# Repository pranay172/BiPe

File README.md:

# BiPe

BiPe is a small wheeled biped: two legs, a wheel at the end of each, and a
binocular head pod. It balances on its wheels, drives, turns, crouches and
stands, gets back up after a fall, and can follow a person wearing an
AprilTag. It is about 1.8 kg.

The robot was designed in full before anything is built: CAD with real parts,
circuit boards, firmware, a physics model and two controllers (a classical
one and a learned policy). **Everything here is simulation and design.
Nothing has been built or powered yet.** Results are labelled by what they
are: a layout study, a validated simulation under stated assumptions, or
(later) a hardware result.

The project takes its direction from open, sim-first robots such as Pollen
Robotics' [Microduck](https://github.com/pollen-robotics/microduck): train in
simulation, export a small policy, and publish the recipe so anyone can rerun
it.

## What it can do in simulation

All results are on the full MuJoCo plant: free base, finite motor limits,
physical contact, belt and gear lash, sensor delays and noise, and the same C
firmware the robot runs.

| Area | Result |
|---|---|
| Balance, drive, turn, crouch | A 107-case acceptance suite: pushes, belt and gear lash, mass and friction changes, motor lag, sensor delay and noise, slopes. Classical controller: all 70 robustness-matrix cases and 25 of 27 scenario cases. |
| Speed | 1.2 m/s, 1.25 m/s², 1.0 rad/s turns, 0.3 m/s reverse, on a 44-case speed suite. |
| Falls | Forward and backward tips keep a structural factor of at least 2.06 on every load path. |
| Electronics | Six moteus-c1 drivers on CAN-FD, a Teensy 4.0 carrier, power board; 3.44 ms of the 5 ms control budget; 28–39 min runtime. |
| Person following | Rendered camera frames in the loop with AprilTag detection: 60/60 nominal runs and 101/112 overall, no falls on the nominal plant. |
| Learned policy | Trained with mjlab on MuJoCo Warp. Recovers 89/98 acceptance cases (classical 83/98), all 30 pushes, all 8 belt-range cases, no physical failures, and survives all 92 cases of the M18 fidelity suite (motor, sensor, timing and floor imperfections; classical 88/92). Exported to ONNX and a 48k-parameter C forward pass that matches within 6.3e-7. |
| Get-up | A second policy gets the robot up from a sit or a front or back lean and hands over to the locomotion policy, including from flat on the face or back (M17: legs to their stops for 0.5 s first). M18's version, trained with motor, sensor, timing and floor imperfections: 60/60 held-out randomised falls, 40/40 on a fresh set, and 39/40 and 38/40 on two sets of robots drawn from those imperfections. |
| Sit and stand | A third policy sits the robot down on its shell and stands it up again: 40/40 randomised cycles, each ending within 1.34 mm of the commanded height. |
| Moves and following with the policy | Three expressive moves (crouch bob, spin and stop, wiggle) pass 3/3 nominal and 21/21 variants. Following with the policy: 60/60 nominal runs and 48/52 robustness runs. |

Known gaps are kept in view: the policy passes 35 of 43 speed cases (the
target is 40), the stress suite falls 5.9 % of the time (the target is 5 %),
the get-up misses 3 of 80 starts on robots drawn from the M18 imperfections
(all lying almost flat, two on the back and one on the face) and cannot recover
a robot on its side, and neither the get-up nor the sit has had a structural
falls screen yet. See [docs/results.md](docs/results.md) for the full numbers,
what each one measures, and what is still open.

The classical controller is the power-up default. The learned policy is
selectable and becomes the default only after a bench check on real
hardware.

## Quick start

Linux, Python 3.12 and [uv](https://docs.astral.sh/uv/):

```bash
git clone https://github.com/pranay172/BiPe.git bipe && cd bipe
uv venv .venv --python 3.12
uv pip sync requirements.lock --python .venv/bin/python
export PYTHONPATH=.
.venv/bin/python -m bipe sim        # drive it yourself
```

`bipe sim` opens BiPe in a MuJoCo window, driven by its learned policies on a
CPU. The arrow keys drive and turn, Page Up and Page Down stand taller and
crouch, End sits, Insert stands (or gets up after a fall), Enter pushes it and
F8 knocks it over. `--start sit`, `front_lean` or `back_lean` starts on the
floor, and `python -m bipe sim --help` lists every key. Without a display,
`python -m bipe sim --headless` runs a scripted tour (drive, turn, push, a move,
sit, stand, a fall and a get-up) and prints a verdict for each step.

The sim runs the policies on the lighter training plant, faster than real
time, with exact sensors. Every result in the table above is from the full
plant instead. To record a full-plant shot,

```bash
.venv/bin/python -m bipe.demo record push_recovery     # classical controller, about 2 min
```

writes `local/demo/push_recovery_classical.npz` (standing, then pushes from
behind and in front). To render it to video, to run the learned policy in the
full plant, the test suite or the acceptance cases, see
[docs/getting-started.md](docs/getting-started.md). Full-plant runs of the
learned policies use `requirements-eval.lock` (MuJoCo 3.14 with PyTorch and
mjlab) instead of `requirements.lock`; every full-plant result is judged in that
environment.

## Repository

| Path | What is there |
|---|---|
| `bipe/` | Python: plant, controllers, test suites, RL environment, demo tools |
| `firmware/` | C core (estimator, balance, follower, policy forward pass) and the Teensy images |
| `config/` | Robot dimensions, masses, limits, controller and sensor settings (SI) |
| `cad/` | FreeCAD scripts that build the assembly |
| `electronics/` | KiCad boards |
| `artifacts/` | Generated records: CAD, renders, simulation results, exported policies |
| `docs/` | Milestone plans and results, hardware plan, studies |
| `tests/` | pytest suite |

More detail in [docs/repository-layout.md](docs/repository-layout.md).

## Documentation

- [Getting started](docs/getting-started.md): install, run, render, train.
- [Results](docs/results.md): what the simulations show, and the open gaps.
- [Repository layout](docs/repository-layout.md).
- [Development pipelines](docs/development.md): CAD, boards, firmware
  builds, renders.
- [Behaviours](docs/behaviours.md): one card per behaviour, with its
  limits; the [policy contract](docs/policy-contract.md) they share; the
  [training playbook](docs/training-playbook.md).
- [Milestone log](docs/milestones/README.md): the full plans and records,
  M10 to M18.
- [Hardware build plan](docs/hardware/build-plan.md) and
  [bill of materials](docs/hardware/bom.csv): about $3,600 with a
  single-leg test rig and spares. Nothing is bought yet.

## Roadmap

1. **Done:** M10 to M18, ending with a behaviour set on one policy contract
   (drive, get up, sit and stand, three moves, following), the `bipe sim`
   front door, get-up from flat on the face or back, and a simulation with
   the real robot's likely imperfections plus the bench tests that will
   measure them (November 2026), and this public release.
2. **Next:** policies on the Hugging Face Hub and a browser replay.
3. **Hardware:** bench timing, a single-leg rig with system identification,
   a tethered robot (classical first, then the policy), then retraining on
   measured parameters.

## Licence

- Code, firmware, configuration and scripts: [Apache-2.0](LICENSE).
- CAD models, renders, simulation records and documentation:
  [CC BY-SA 4.0](LICENSE-CAD).
- Circuit boards: [CERN-OHL-P-2.0](LICENSE-HARDWARE).

[NOTICE](NOTICE) has the exact scope of each licence and the third-party
attributions (mjbots moteus protocol, KiCad footprints).

## Acknowledgements

- BiPe's look and proportions were inspired by Beni, the small wheeled camera
  robot by [Mondo Robotics](https://www.mondorobotics.com/). BiPe is an
  independent project, not affiliated with or endorsed by Mondo Robotics. No
  Mondo designs or CAD were used; the exterior was drawn from public imagery.
- The sim-first approach follows Pollen Robotics'
  [Microduck](https://github.com/pollen-robotics/microduck): train in
  simulation, export a small policy, and publish the recipe.

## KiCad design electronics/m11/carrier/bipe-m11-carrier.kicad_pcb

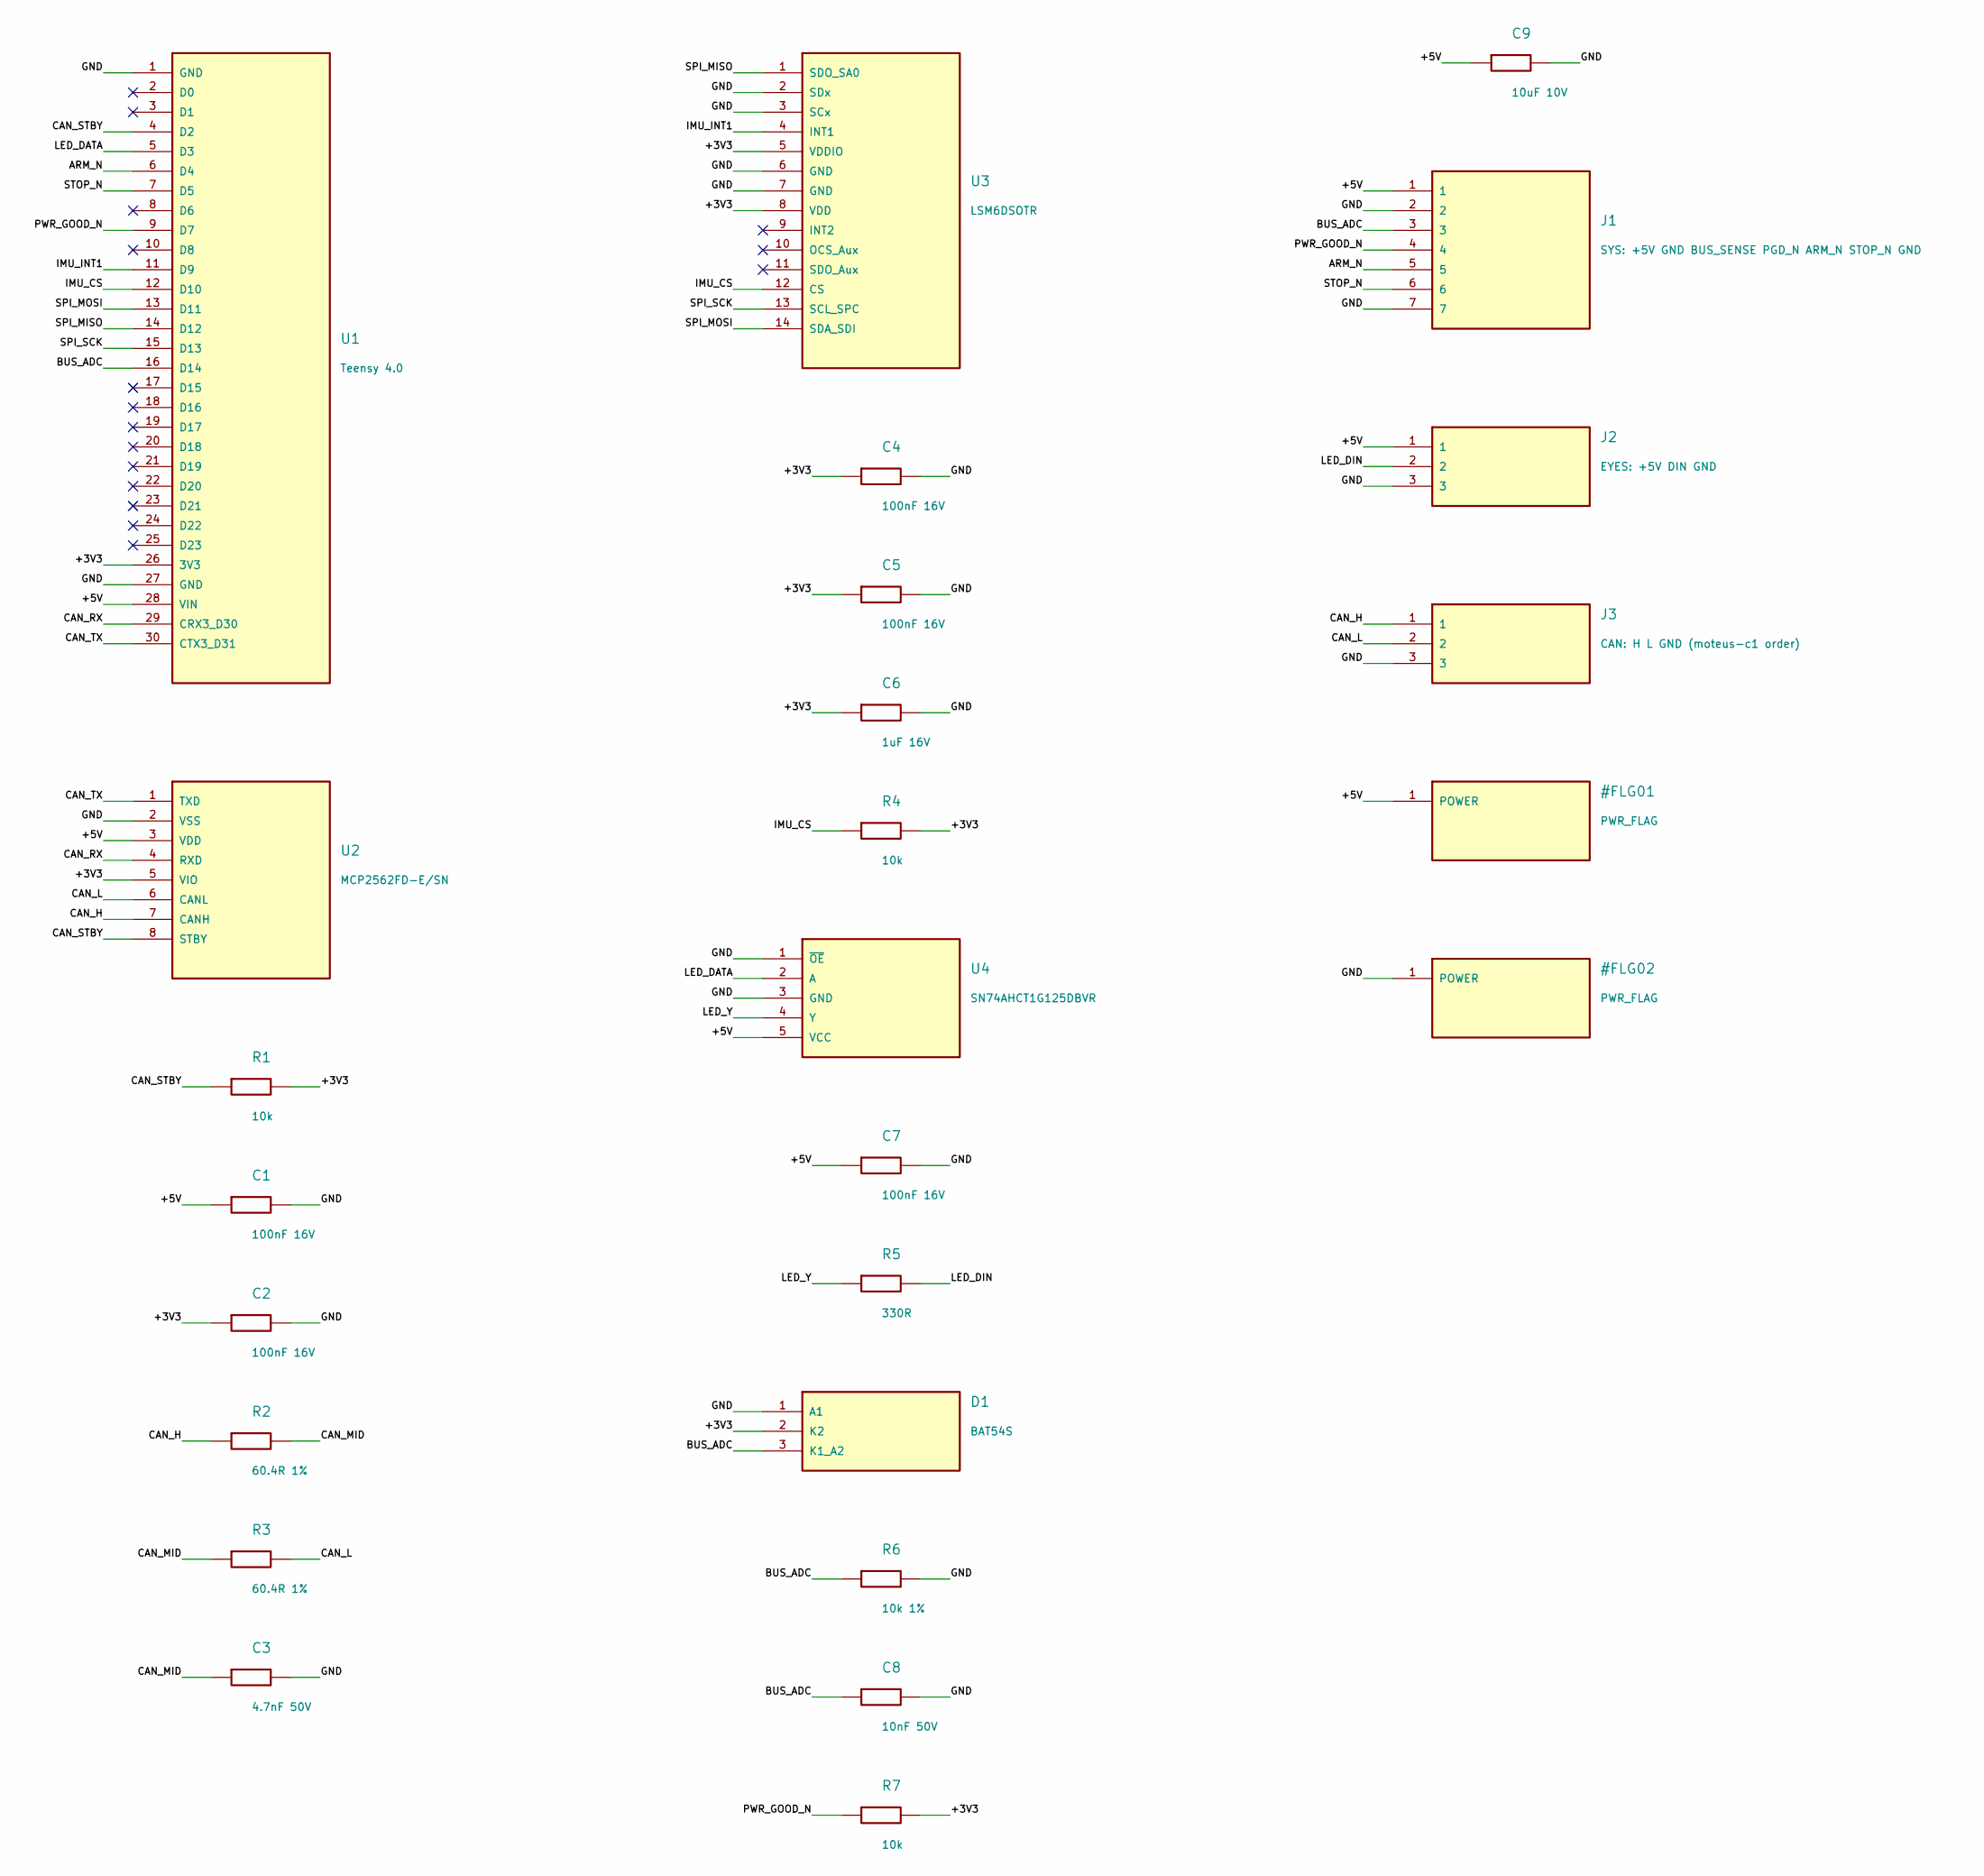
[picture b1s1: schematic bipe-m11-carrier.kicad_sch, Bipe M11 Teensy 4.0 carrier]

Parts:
C1, C2, C4, C5, C7: 100nF 16V; C_0603_1608Metric; MPN 100nF 16V
C3: 4.7nF 50V; C_0603_1608Metric; MPN 4.7nF 50V
C6: 1uF 16V; C_0603_1608Metric; MPN 1uF 16V
C8: 10nF 50V; C_0603_1608Metric; MPN 10nF 50V
C9: 10uF 10V; C_0805_2012Metric; MPN 10uF 10V
D1: BAT54S; SOT-23; MPN BAT54S; LCSC C2828465
J1: SYS: +5V GND BUS_SENSE PGD_N ARM_N STOP_N GND; JST_PH_B7B-PH-K_1x07_P2.00mm_Vertical; MPN B7B-PH-K-S(LF)(SN); LCSC C157981
J2: EYES: +5V DIN GND; JST_PH_B3B-PH-K_1x03_P2.00mm_Vertical; MPN B3B-PH-K-S(LF)(SN); LCSC C131339
J3: CAN: H L GND (moteus-c1 order); JST_PH_B3B-PH-K_1x03_P2.00mm_Vertical; MPN B3B-PH-K-S(LF)(SN); LCSC C131339
R1, R4, R7: 10k; R_0603_1608Metric; MPN 0603 10k
R2, R3: 60.4R 1%; R_0603_1608Metric; MPN 0603 60.4R 1%
R5: 330R; R_0603_1608Metric; MPN 0603 330R
R6: 10k 1%; R_0603_1608Metric; MPN 0603 10k 1%
U1: Teensy 4.0; Teensy40_Carrier; MPN PJRC Teensy 4.0 (VUSB-VIN pad cut)
U2: MCP2562FD-E/SN; SOIC-8_3.9x4.9mm_P1.27mm; MPN MCP2562FD-E/SN; LCSC C124016
U3: LSM6DSOTR; LGA-14_3x2.5mm_P0.5mm_LayoutBorder3x4y; MPN LSM6DSOTR; LCSC C2655100
U4: SN74AHCT1G125DBVR; SOT-23-5; MPN SN74AHCT1G125DBVR; LCSC C7484

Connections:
/+3V3: C2.1, C4.1, C5.1, C6.1, D1.2 (K2), R1.2, R4.2, R7.2, U1.26 (3V3), U2.5 (VIO), U3.5 (VDDIO), U3.8 (VDD)
/+5V: C1.1, C7.1, C9.1, J1.1, J2.1, U1.28 (VIN), U2.3 (VDD), U4.5 (VCC)
/ARM_N: J1.5, U1.6 (D4)
/BUS_ADC: C8.1, D1.3 (K1_A2), J1.3, R6.1, U1.16 (D14)
/CAN_H: J3.1, R2.1, U2.7 (CANH)
/CAN_L: J3.2, R3.2, U2.6 (CANL)
/CAN_MID: C3.1, R2.2, R3.1
/CAN_RX: U1.29 (CRX3_D30), U2.4 (RXD)
/CAN_STBY: R1.1, U1.4 (D2), U2.8 (STBY)
/CAN_TX: U1.30 (CTX3_D31), U2.1 (TXD)
/GND: C1.2, C2.2, C3.2, C4.2, C5.2, C6.2, C7.2, C8.2, C9.2, D1.1 (A1), J1.2, J1.7, J2.3, J3.3, R6.2, U1.1 (GND), U1.27 (GND), U2.2 (VSS), U3.2 (SDx), U3.3 (SCx), U3.6 (GND), U3.7 (GND), U4.1 (~OE), U4.3 (GND)
/IMU_CS: R4.1, U1.12 (D10), U3.12 (CS)
/IMU_INT1: U1.11 (D9), U3.4 (INT1)
/LED_DATA: U1.5 (D3), U4.2 (A)
/LED_DIN: J2.2, R5.2
/LED_Y: R5.1, U4.4 (Y)
/PWR_GOOD_N: J1.4, R7.1, U1.9 (D7)
/SPI_MISO: U1.14 (D12), U3.1 (SDO_SA0)
/SPI_MOSI: U1.13 (D11), U3.14 (SDA_SDI)
/SPI_SCK: U1.15 (D13), U3.13 (SCL_SPC)
/STOP_N: J1.6, U1.7 (D5)

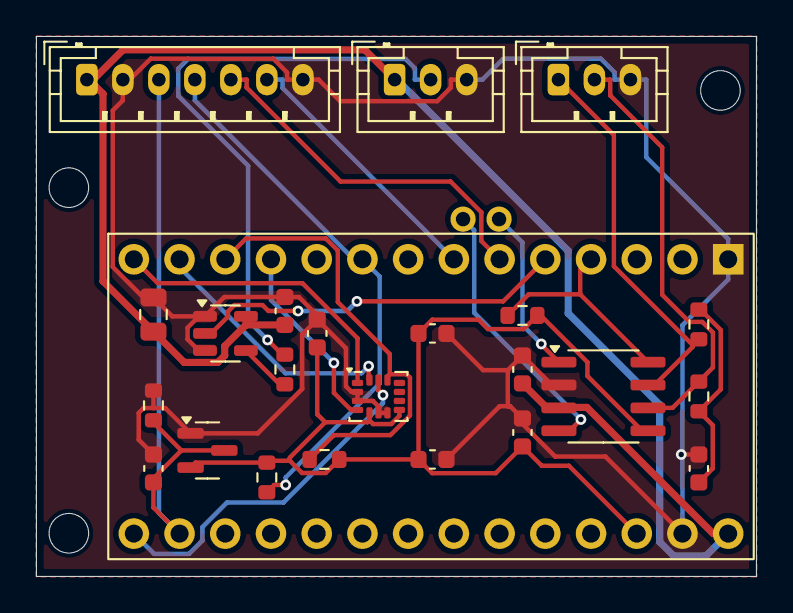
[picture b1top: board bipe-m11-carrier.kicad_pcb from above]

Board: 2 copper layers, 40.0 x 30.0 mm, 27 parts (0 on the bottom side), 21 nets.

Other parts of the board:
H1, H2, H3: MountingHole_2.2mm_M2

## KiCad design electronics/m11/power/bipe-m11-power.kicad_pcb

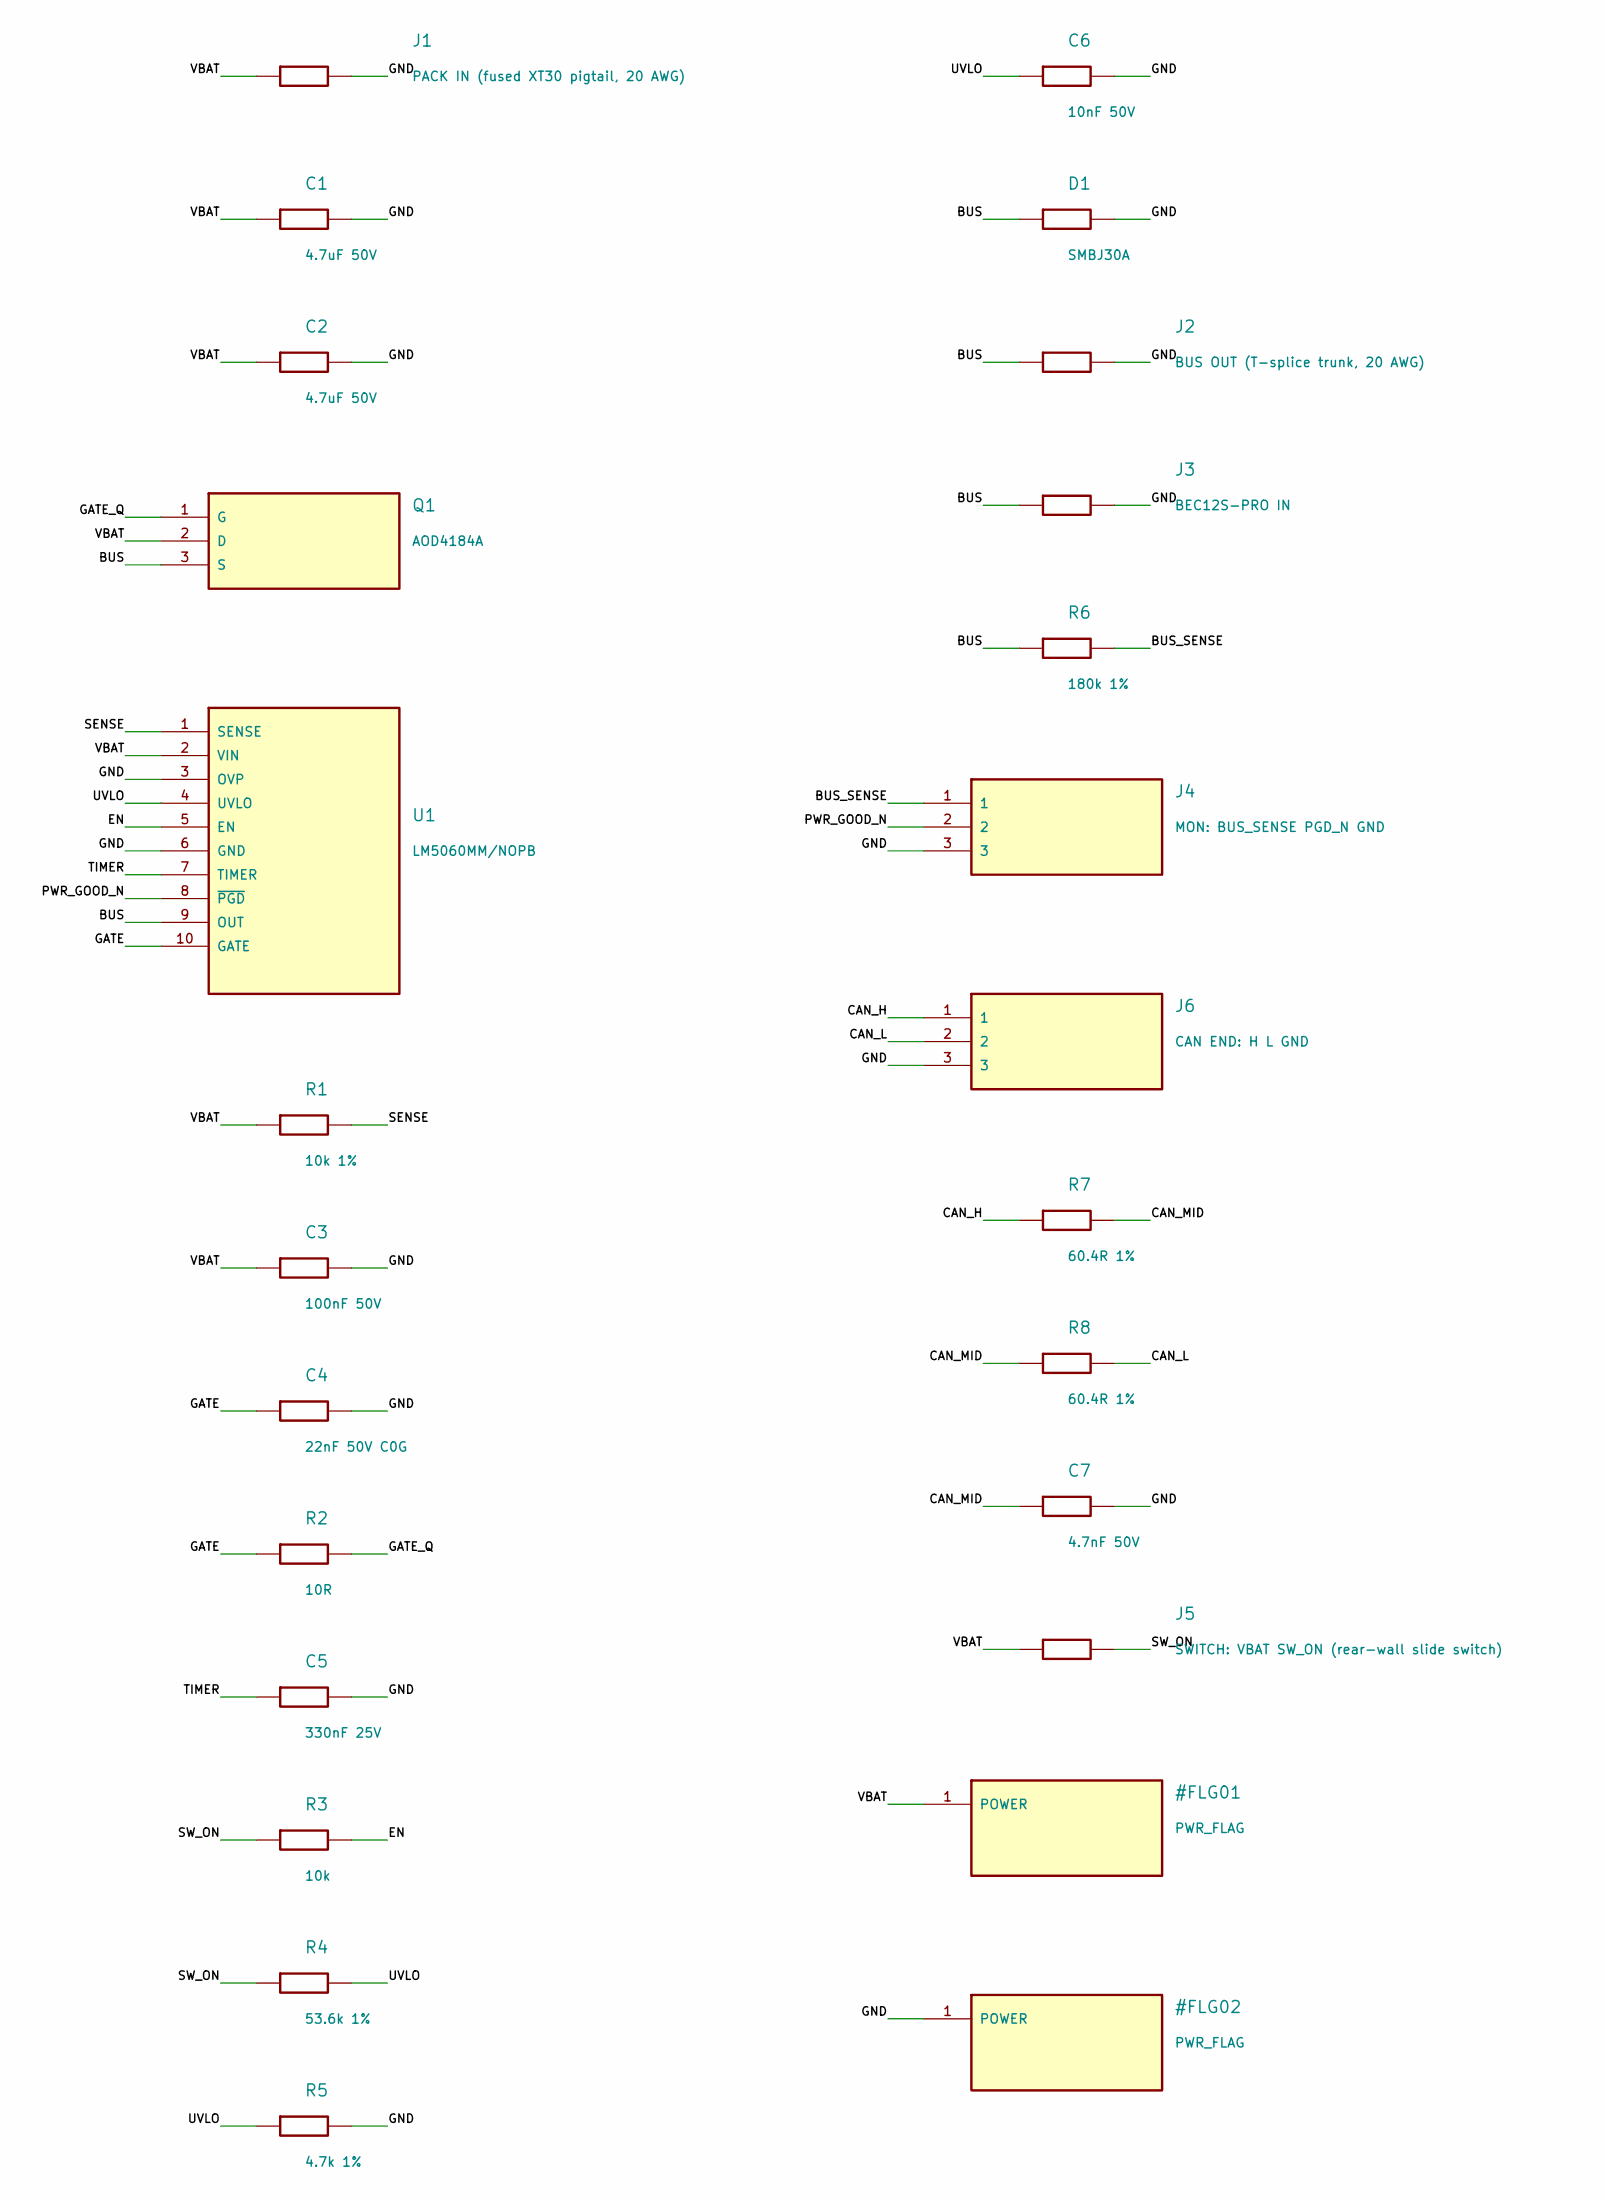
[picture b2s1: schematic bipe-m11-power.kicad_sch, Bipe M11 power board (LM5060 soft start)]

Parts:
C1, C2: 4.7uF 50V; C_1206_3216Metric; MPN 4.7uF 50V
C3: 100nF 50V; C_0603_1608Metric; MPN 100nF 50V
C4: 22nF 50V C0G; C_0603_1608Metric; MPN 22nF 50V C0G
C5: 330nF 25V; C_0603_1608Metric; MPN 330nF 25V
C6: 10nF 50V; C_0603_1608Metric; MPN 10nF 50V
C7: 4.7nF 50V; C_0603_1608Metric; MPN 4.7nF 50V
D1: SMBJ30A; D_SMB; MPN SMBJ30A-13-F; LCSC C135065
J1: PACK IN (fused XT30 pigtail, 20 AWG); SolderWire-0.5sqmm_1x02_P4.6mm_D0.9mm_OD2.1mm; MPN PACK IN (fused XT30 pigtail, 20 AWG)
J2: BUS OUT (T-splice trunk, 20 AWG); SolderWire-0.5sqmm_1x02_P4.6mm_D0.9mm_OD2.1mm; MPN BUS OUT (T-splice trunk, 20 AWG)
J3: BEC12S-PRO IN; SolderWire-0.25sqmm_1x02_P4.2mm_D0.65mm_OD1.7mm; MPN BEC12S-PRO IN
J4: MON: BUS_SENSE PGD_N GND; JST_PH_B3B-PH-K_1x03_P2.00mm_Vertical; MPN B3B-PH-K-S(LF)(SN); LCSC C131339
J5: SWITCH: VBAT SW_ON (rear-wall slide switch); JST_PH_B2B-PH-K_1x02_P2.00mm_Vertical; MPN B2B-PH-K-S(LF)(SN); LCSC C131337
J6: CAN END: H L GND; JST_PH_B3B-PH-K_1x03_P2.00mm_Vertical; MPN B3B-PH-K-S(LF)(SN); LCSC C131339
Q1: AOD4184A; TO-252-2; MPN AOD4184A; LCSC C99124
R1: 10k 1%; R_0603_1608Metric; MPN 0603 10k 1%
R2: 10R; R_0603_1608Metric; MPN 0603 10R
R3: 10k; R_0603_1608Metric; MPN 0603 10k
R4: 53.6k 1%; R_0603_1608Metric; MPN 0603 53.6k 1%
R5: 4.7k 1%; R_0603_1608Metric; MPN 0603 4.7k 1%
R6: 180k 1%; R_0603_1608Metric; MPN 0603 180k 1%
R7, R8: 60.4R 1%; R_0603_1608Metric; MPN 0603 60.4R 1%
U1: LM5060MM/NOPB; VSSOP-10_3x3mm_P0.5mm; MPN LM5060MM/NOPB; LCSC C74456

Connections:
/BUS: D1.1, J2.1, J3.1, Q1.3 (S), R6.1, U1.9 (OUT)
/BUS_SENSE: J4.1, R6.2
/CAN_H: J6.1, R7.1
/CAN_L: J6.2, R8.2
/CAN_MID: C7.1, R7.2, R8.1
/EN: R3.2, U1.5 (EN)
/GATE: C4.1, R2.1, U1.10 (GATE)
/GATE_Q: Q1.1 (G), R2.2
/GND: C1.2, C2.2, C3.2, C4.2, C5.2, C6.2, C7.2, D1.2, J1.2, J2.2, J3.2, J4.3, J6.3, R5.2, U1.3 (OVP), U1.6 (GND)
/PWR_GOOD_N: J4.2, U1.8 (~PGD)
/SENSE: R1.2, U1.1 (SENSE)
/SW_ON: J5.2, R3.1, R4.1
/TIMER: C5.1, U1.7 (TIMER)
/UVLO: C6.1, R4.2, R5.1, U1.4 (UVLO)
/VBAT: C1.1, C2.1, C3.1, J1.1, J5.1, Q1.2 (D), R1.1, U1.2 (VIN)

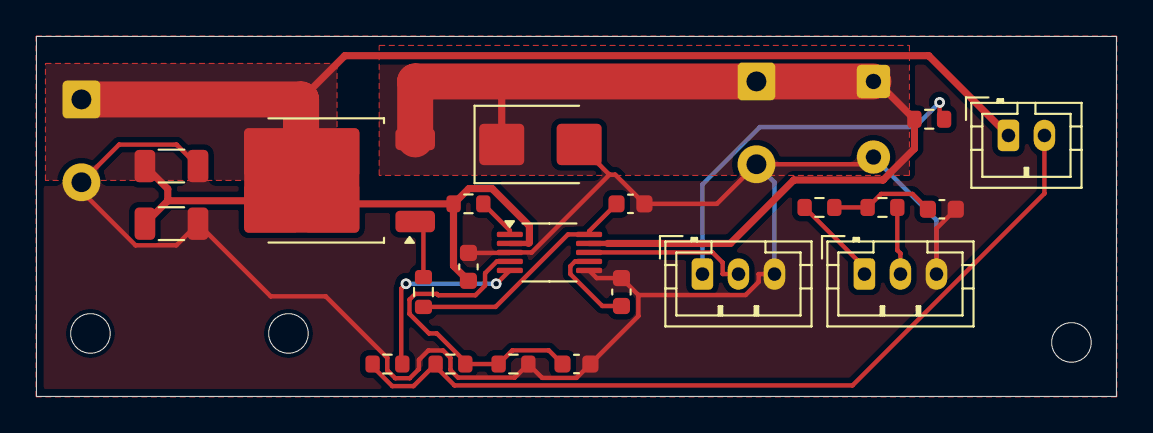
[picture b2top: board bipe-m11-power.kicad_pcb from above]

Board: 2 copper layers, 60.0 x 20.0 mm, 27 parts (0 on the bottom side), 15 nets.

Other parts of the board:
H1, H2, H3: MountingHole_2.2mm_M2

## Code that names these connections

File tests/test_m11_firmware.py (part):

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    pins = teensy_pins()
    # Teensy 4.0: CAN3 on the bottom pads 30 (CRX3) and 31 (CTX3); SPI0 on 11/12/13;
    # A0 is pin 14.
    assert (pins["CAN_RX"], pins["CAN_TX"]) == (30, 31)
    assert (pins["SPI_MOSI"], pins["SPI_MISO"], pins["SPI_SCK"]) == (11, 12, 13)
    assert pins["BUS_ADC"] == 14
    assert len(set(pins.values())) == len(pins)


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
